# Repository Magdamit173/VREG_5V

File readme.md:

# 5V Voltage Regulator PCB Project

This project contains the design files for a 5V voltage regulator circuit implemented in both KiCad and NI Multisim.

## PCB Preview
The image above shows a 3D rendering of the PCB design, giving a clear view of component placement and board layout.

## Project Structure

- `VREG_5V.kicad_sch` - KiCad schematic file
- `VREG_5V.kicad_pcb` - KiCad PCB layout file
- `VREG_5V.kicad_pro` - KiCad project file
- `NI Multisim/VREG_5V.ms14` - NI Multisim simulation file
- `Plot/` - Generated output files and documentation
- `VREG_5V-backups/` - Automatic backup files

## Description

This project implements a 5V voltage regulator circuit, designed using KiCad for PCB layout and verified through NI Multisim simulation. The circuit provides a stable 5V DC output that can be used for various electronic applications.

## Software Used

- KiCad - For schematic capture and PCB design
- NI Multisim - For circuit simulation and verification
- FreeRouting - For PCB auto-routing (dsn file included)

## Files and Their Purpose

### KiCad Files
- `.kicad_sch` - Contains the electronic schematic
- `.kicad_pcb` - Contains the PCB layout
- `.kicad_pro` - Project settings and configuration
- `.kicad_prl` - Local project settings
- `fp-info-cache` - Footprint cache file

### Additional Files
- `freerouting.dsn` - Design file for auto-routing
- Lock files (`*.lck`) - Temporary files created when the project is open

## Documentation (Not yet)

The `Plot/` directory contains generated documentation including:
- Gerber files
- Assembly drawings
- BOM (Bill of Materials)
- PDF schematics

## Backup Information

The project maintains automatic backups in the `VREG_5V-backups/` directory for safety and version control purposes.

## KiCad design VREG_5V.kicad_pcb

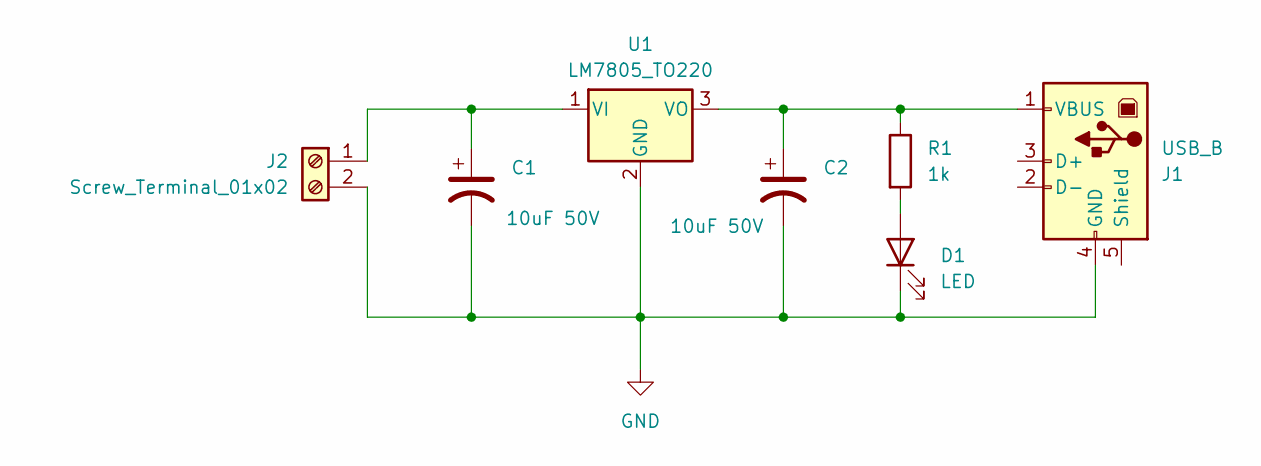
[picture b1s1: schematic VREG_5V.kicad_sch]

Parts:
C1, C2: 10uF 50V; CP_Radial_D6.3mm_P2.50mm
D1: LED; LED_D5.0mm
J1: USB_B; USB_A_Molex_67643_Horizontal
J2: Screw_Terminal_01x02; TerminalBlock_Phoenix_MKDS-1,5-2-5.08_1x02_P5.08mm_Horizont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
R1: 1k; R_Axial_DIN0207_L6.3mm_D2.5mm_P2.54mm_Vertical
U1: LM7805_TO220; TO-220-3_Vertical

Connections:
GND: C1.2, C2.2, D1.1 (K), J1.4 (GND), J2.2, U1.2 (GND)
unnamed: D1.2 (A), R1.2
unnamed: C2.1, J1.1 (VBUS), R1.1, U1.3 (VO)
unnamed: C1.1, J2.1, U1.1 (VI)

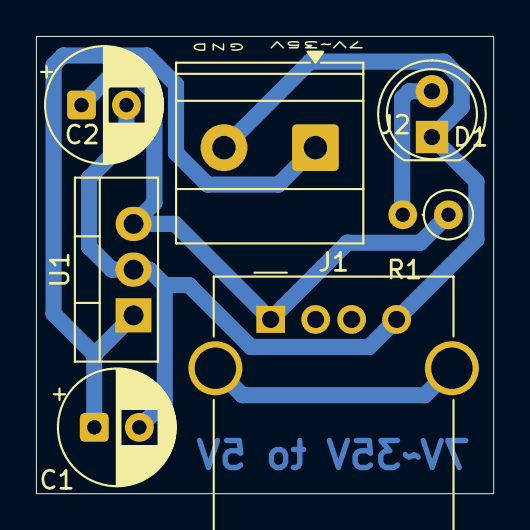
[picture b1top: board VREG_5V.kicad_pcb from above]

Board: 2 copper layers, 25.4 x 25.4 mm, 7 parts (0 on the bottom side), 4 nets.

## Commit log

2025-11-04 11.5.2025
2025-11-07 11.7.2025
